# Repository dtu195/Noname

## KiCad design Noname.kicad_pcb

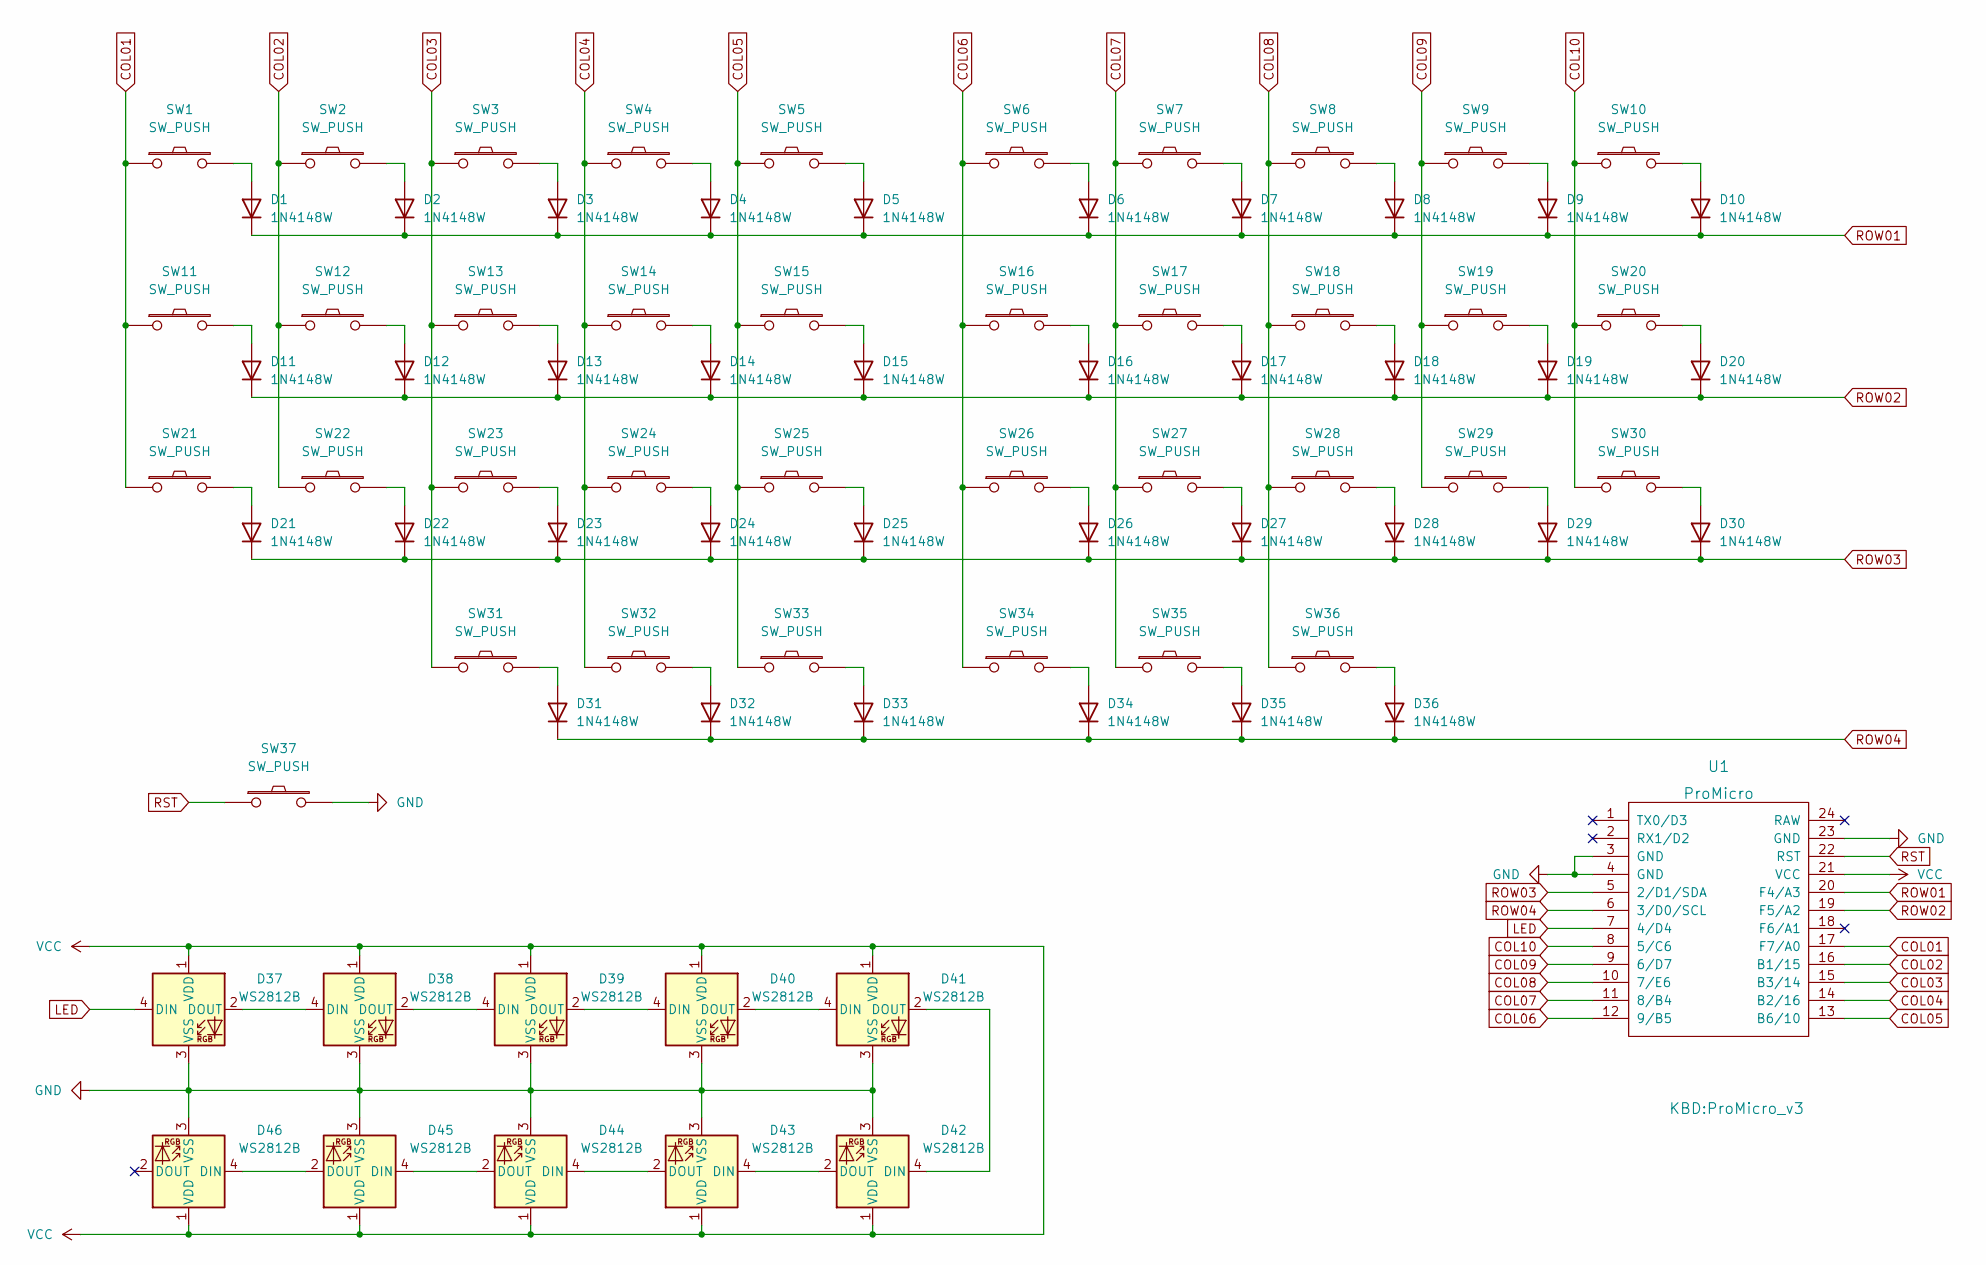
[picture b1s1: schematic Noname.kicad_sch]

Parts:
D1, D2, D3, D4, D5, D6, D7, D8, D9, D10, D11, D12, D13, D14, D15, D16, D17, D18, D19, D20, D21, D22, D23, D24, D25, D26, D27, D28, D29, D30, D31, D32, D33, D34, D35, D36: 1N4148W; D3_SMD_v2
D37, D38, D39, D40, D41, D42, D43, D44, D45, D46: WS2812B; LED_WS2812B-PLCC4
SW1, SW2, SW3, SW4, SW5, SW6, SW7, SW8, SW9, SW10, SW11, SW12, SW13, SW14, SW15, SW16, SW17, SW18, SW19, SW20, SW21, SW22, SW23, SW24, SW25, SW26, SW27, SW28, SW29, SW30, SW31, SW32, SW35, SW36: SW_PUSH; CherryMX_Hotswap
SW33, SW34: SW_PUSH; CherryMX_Hotswap_1.5u
SW37: SW_PUSH; SW_SPST_TL3342
U1: ProMicro; ProMicro_v3

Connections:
COL01: SW1.1, SW11.1, SW21.1, U1.17 (F7/A0)
COL02: SW2.1, SW12.1, SW22.1, U1.16 (B1/15)
COL03: SW3.1, SW13.1, SW23.1, SW31.1, U1.15 (B3/14)
COL04: SW4.1, SW14.1, SW24.1, SW32.1, U1.14 (B2/16)
COL05: SW5.1, SW15.1, SW25.1, SW33.1, U1.13 (B6/10)
COL06: SW6.1, SW16.1, SW26.1, SW34.1, U1.12 (9/B5)
COL07: SW7.1, SW17.1, SW27.1, SW35.1, U1.11 (8/B4)
COL08: SW8.1, SW18.1, SW28.1, SW36.1, U1.10 (7/E6)
COL09: SW9.1, SW19.1, SW29.1, U1.9 (6/D7)
COL10: SW10.1, SW20.1, SW30.1, U1.8 (5/C6)
GND: D37.3 (VSS), D38.3 (VSS), D39.3 (VSS), D40.3 (VSS), D41.3 (VSS), D42.3 (VSS), D43.3 (VSS), D44.3 (VSS), D45.3 (VSS), D46.3 (VSS), SW37.2, U1.3 (GND), U1.4 (GND), U1.23 (GND)
LED: D37.4 (DIN), U1.7 (4/D4)
unnamed: D1.2 (A), SW1.2
unnamed: D2.2 (A), SW2.2
unnamed: D3.2 (A), SW3.2
unnamed: D4.2 (A), SW4.2
unnamed: D5.2 (A), SW5.2
unnamed: D6.2 (A), SW6.2
unnamed: D7.2 (A), SW7.2
unnamed: D8.2 (A), SW8.2
unnamed: D9.2 (A), SW9.2
unnamed: D10.2 (A), SW10.2
unnamed: D11.2 (A), SW11.2
unnamed: D12.2 (A), SW12.2
unnamed: D13.2 (A), SW13.2
unnamed: D14.2 (A), SW14.2
unnamed: D15.2 (A), SW15.2
unnamed: D16.2 (A), SW16.2
unnamed: D17.2 (A), SW17.2
unnamed: D18.2 (A), SW18.2
unnamed: D19.2 (A), SW19.2
unnamed: D20.2 (A), SW20.2
unnamed: D21.2 (A), SW21.2
unnamed: D22.2 (A), SW22.2
unnamed: D23.2 (A), SW23.2
unnamed: D24.2 (A), SW24.2
unnamed: D25.2 (A), SW25.2
unnamed: D26.2 (A), SW26.2
unnamed: D27.2 (A), SW27.2
unnamed: D28.2 (A), SW28.2
unnamed: D29.2 (A), SW29.2
unnamed: D30.2 (A), SW30.2
unnamed: D31.2 (A), SW31.2
unnamed: D32.2 (A), SW32.2
unnamed: D33.2 (A), SW33.2
unnamed: D34.2 (A), SW34.2
unnamed: D35.2 (A), SW35.2
unnamed: D36.2 (A), SW36.2
unnamed: D37.2 (DOUT), D38.4 (DIN)
unnamed: D38.2 (DOUT), D39.4 (DIN)
unnamed: D39.2 (DOUT), D40.4 (DIN)
unnamed: D40.2 (DOUT), D41.4 (DIN)
unnamed: D41.2 (DOUT), D42.4 (DIN)
unnamed: D42.2 (DOUT), D43.4 (DIN)
unnamed: D43.2 (DOUT), D44.4 (DIN)
unnamed: D44.2 (DOUT), D45.4 (DIN)
unnamed: D45.2 (DOUT), D46.4 (DIN)
ROW01: D1.1 (K), D2.1 (K), D3.1 (K), D4.1 (K), D5.1 (K), D6.1 (K), D7.1 (K), D8.1 (K), D9.1 (K), D10.1 (K), U1.20 (F4/A3)
ROW02: D11.1 (K), D12.1 (K), D13.1 (K), D14.1 (K), D15.1 (K), D16.1 (K), D17.1 (K), D18.1 (K), D19.1 (K), D20.1 (K), U1.19 (F5/A2)
ROW03: D21.1 (K), D22.1 (K), D23.1 (K), D24.1 (K), D25.1 (K), D26.1 (K), D27.1 (K), D28.1 (K), D29.1 (K), D30.1 (K), U1.5 (2/D1/SDA)
ROW04: D31.1 (K), D32.1 (K), D33.1 (K), D34.1 (K), D35.1 (K), D36.1 (K), U1.6 (3/D0/SCL)
RST: SW37.1, U1.22 (RST)
VCC: D37.1 (VDD), D38.1 (VDD), D39.1 (VDD), D40.1 (VDD), D41.1 (VDD), D42.1 (VDD), D43.1 (VDD), D44.1 (VDD), D45.1 (VDD), D46.1 (VDD), U1.21 (VCC)

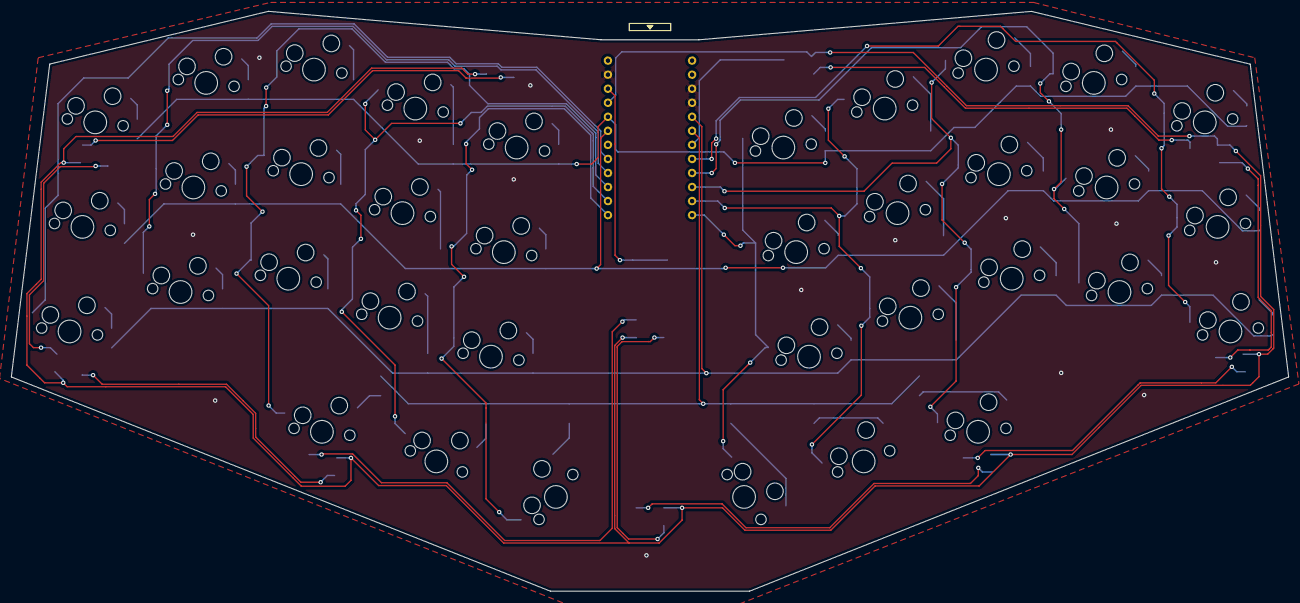
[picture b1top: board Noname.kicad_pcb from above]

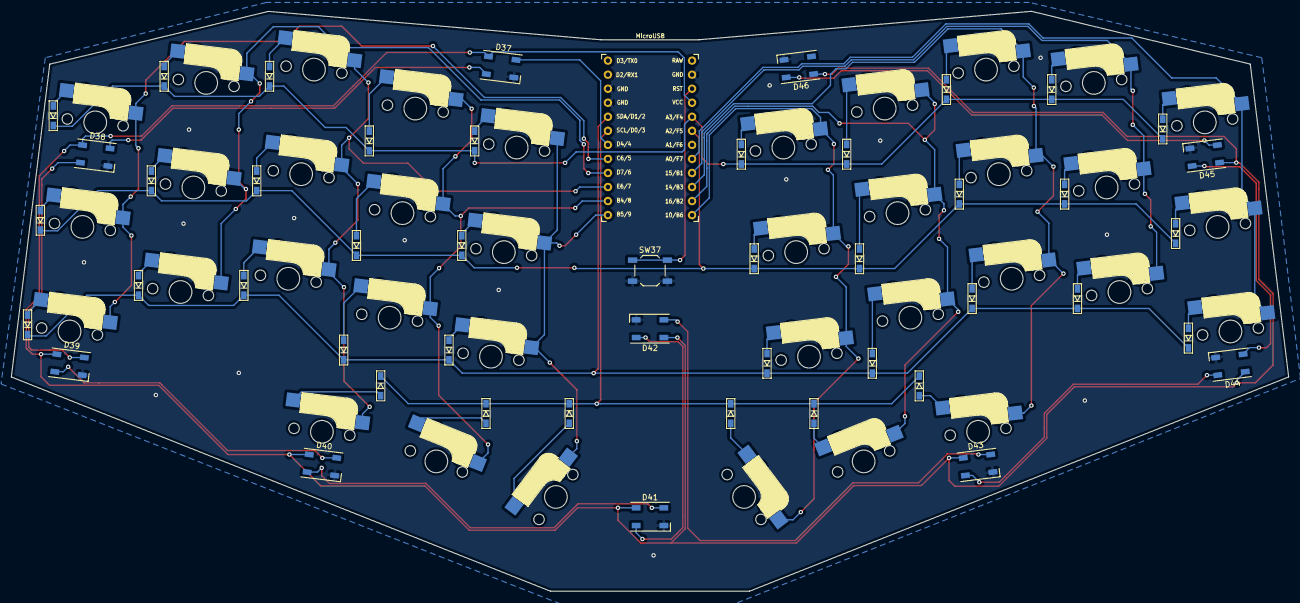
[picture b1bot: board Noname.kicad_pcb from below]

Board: 2 copper layers, 231.0 x 104.9 mm, 84 parts (47 on the bottom side), 63 nets.

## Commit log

2022-05-31 First version
2022-05-31 Add case design
